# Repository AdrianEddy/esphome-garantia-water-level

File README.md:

# Garantia water tank level sensor for ESPHome / KNX

So you have an old-fashioned water tank level module like this one

and you want to see the percentage in your Home Assistant dashboard? Let's do it!

Three ways to get there:

- **V1** – keep the original controller, sniff its display signals with an ESP32 (below).
- **V2** – replace the controller with a small board that talks to the tank sensor directly:
  analog 0–5 V output (KNX or ESP32 ADC), or ESP32 pulse counting with a single transistor. [Jump to V2](#v2--replacing-the-controller).
- **V3** – a KNX device of its own: one small board on the KNX bus that powers the sensor and reports level, frequency
  and faults straight to KNX, with calibration from Home Assistant and a safe top-up valve control. [Jump to V3](#v3--knx-device).

---

# V1 – reading the original controller

## 0. [What? How?](HOW.md)

## 1. Required hardware
- [ESP32-S3-Zero](https://www.waveshare.com/esp32-s3-zero.htm)
- [TXS0108E](https://aliexpress.com/i/4001172918547.html)

## 2. Connections

You also have to replace the on-board voltage regulator **8L05A** to a more powerful one [KF50BD-TR](https://www.st.com/resource/en/datasheet/kfxx.pdf)

## 3. ESPHome component

```yaml
esphome:
  name: garantia-water-level
  platformio_options: # needed for ESP32-S3
    board_build.flash_mode: dio

esp32:
  board: adafruit_feather_esp32s3
  framework:
    type: esp-idf

external_components:
  - source: github://AdrianEddy/esphome-garantia-water-level
    components: [ garantia-water-level ]

sensor:
  - platform: garantia-water-level
```

## Final assembly

## See it in action

---

# V2 – replacing the controller

The tank-side electronics (the small box in the tank + the red/white sensor cord) are fine and stay untouched.
Only the indoor box gets replaced.

## What the sensor actually does (research, short version)

Reverse-engineered from the original PCB and measured with a scope – **the manual is misleading here**:

- The tank box is a capacitance-to-frequency converter on a **2-wire current loop**: the controller sends +12 V on one RCA contact, the sensor's return current comes back on the other contact through a **110 Ω shunt** (2×220 Ω on the original PCB). The current is pulsed – that's the signal.
- Signal across the shunt: **≈1.7 V pk-pk**, square-ish, ~35/65 duty, on ~3 V DC (the sensor draws ≈27 mA).
- **Frequency: ~145 Hz with an empty tank, ~25 Hz with a full tank.** More water → lower frequency.
  The "200 Hz – 20 kHz" in the manual is *not* what comes down the cable – ignore it.
- Level is **linear in period**, not frequency: `level = (1/f − 1/f_empty) / (1/f_full − 1/f_empty)`.
- The original controller is an ATtiny2313 counting that frequency with its internal comparator. No magic.

Conclusions that saved parts:
- The signal is big enough that **no comparator is needed** – an LM2917 or a single transistor reads it directly.
  (Only if your sensor variant gives < 300 mVpp would you need an LM393-style comparator in front.)
- The one critical component is the LM2917 timing cap C1 – it sets the gain: **C0G / U2J / film only**, never X7R.
- Frequencies are installation specific (cord length, tank). **Measure yours** before picking values.
- If your original controller reads unstable, check its wall adapter first – ours had sagged to 10 V.

## Measure your sensor first

1. Power the tank box with 12 V through a 110 Ω shunt to GND (the V2 board does exactly this).
2. Scope across the shunt, **AC coupling**, 0.5 V/div, 10 ms/div. Note the frequency.
3. Record `f_empty` (pump can't take more out) and `f_full` (water at the overflow). Optional sanity check:
   a period-linear sensor sits at `2 / (1/f_empty + 1/f_full)` at 50 % (≈43 Hz for 145/25).

Everything below is parameterised on `f_empty` and `f_full`.

## Which option?

| You want | Use |
|---|---|
| An **analog 0–5 V signal** – KNX analog input (e.g. ABB AE/A 2.1) or ESP32 ADC | **Option A – LM2917** |
| Just an ESP32 in Home Assistant, best accuracy, fewest parts | **Option B – transistor + `pulse_meter`** |

Common to both: 12 V DC supply, RCA jack (contact A = +12 V feed, contact B = signal), 110 Ω shunt from signal to GND, one common GND.

**Power:** a Mean Well HDR-15-12 works, but in the KNX version I skipped the extra PSU altogether: the **yellow/white pair** of the KNX cable
carries the 30 V *auxiliary* (unchoked) output of the KNX power supply, and **Traco Power TMR 2412** drops it to 12.0 V.
 The board draws ~20 mA at 30 V. Take it only from the auxiliary output / yellow-white pair – **never from the
red/black bus pair**, which carries the telegrams and must not see a switching load. **Do not** use a cheap DC-DC buck module (LM2596-type) - 12V GND MUST be isolated from KNX GND

---

### Option A – LM2917 frequency-to-voltage (KNX / analog)

**KiCad project (schematic + PCB, JLCPCB-ready):** [hardware/garantia-lm2917-kicad.zip](hardware/garantia-lm2917-kicad.zip)
– the 1206/SOIC parts can be assembled by JLCPCB PCBA; DIP LM2917, trimmer and connectors are hand-soldered.

Transfer function: **V_OUT = 7.56 V × f × C1 × R1**. Design for ~4.5 V at `f_empty` (headroom below the 5 V input range):

```
C1 × R1 = 4.5 / (7.56 × f_empty)          # f_empty = 145 Hz → 4.1e-3
pick C1 so R1 lands mid-trimmer (47k fixed + 100k trim):  145 Hz → C1 = 47 nF, R1 ≈ 87 k
charge-pump limit:  f_empty < 140e-6 / (C1 × 7.56)        # 47 nF → 394 Hz max
```

Values as built (f_empty 145 Hz, f_full 25 Hz):

| Ref | Value | Notes |
|---|---|---|
| R1 | 110 Ω (or 2×220 Ω) | shunt |
| C3, R2, R3 | 470 nF film, 22 k, 10 k | AC coupling into pin 1 |
| R4, C4, C5 | 470 Ω, 1 µF, 100 nF | pin 6 (internal 7.56 V zener) |
| C1 | **47 nF C0G / U2J / film** | pin 2 – gain critical |
| R5 + RV1, C2 | 47 k + 100 k trimmer (rheostat), 10 µF | pin 3 – gain trim + filter |
| R6, R7 | 10 k, 470 Ω | output load + series; pin 7 strapped to pin 4, pin 5 to +12 V |

Output: empty 145 Hz → **4.50 V**, full 25 Hz → **0.78 V**. Voltage at level L: `V = 4.5 / (1 + (f_empty/f_full − 1)·L)`.

**Trim:** turn RV1 until `OUT = 4.5 × f / f_empty` at any known frequency (full tank → 0.78 V).

**KNX (ABB AE/A 2.1):** channel = voltage 0–5 V, output as 4-byte float, lower 0 % → 0, upper 100 % → 5 (bus value = volts).
Filter *low* (the 64-sample filter turns a sensor failure into a 60 s fake "filling" ramp). Send on change ≥1 % + cyclic 5 min.
Threshold 1 (valve): ON above 3.04 V (10 %), OFF below 2.86 V (12 %). Threshold 2 (fault): ON below 0.40 V.

**Home Assistant (KNX):**
```yaml
knx:
  sensor:
    - name: "Tank voltage"
      state_address: "5/3/4"
      type: 4byte_float
      device_class: voltage

template:
  - sensor:
      - name: "Rainwater tank level"
        unit_of_measurement: "%"
        state_class: measurement
        state: >
          {% set v = states('sensor.tank_voltage') | float(0) %}
          {% set ve = 4.50 %}   {# voltage at f_empty #}
          {% set vf = 0.78 %}   {# voltage at f_full  #}
          {% if v < 0.4 %}{{ none }}
          {% else %}{{ [0, [100, ((1/v - 1/ve) / (1/vf - 1/ve) * 100) | round(0)] | min] | max }}
          {% endif %}
  - binary_sensor:
      - name: "Rainwater tank sensor fault"
        device_class: problem
        state: "{{ states('sensor.tank_voltage') | float(0) < 0.4 }}"
```

**ESP32 ADC instead of KNX:** 10 k / 10 k divider from OUT to GND, tap → GPIO4 (ADC1), common GND.
```yaml
sensor:
  - platform: adc
    pin: GPIO4
    id: tank_v
    attenuation: 12db
    update_interval: 1s
    filters:
      - median: { window_size: 15, send_every: 5 }
      - multiply: 2.0
  - platform: template
    name: "Rainwater tank level"
    unit_of_measurement: "%"
    lambda: |-
      const float VE = 4.50, VF = 0.78;
      float v = id(tank_v).state;
      if (v < 0.4) return NAN;
      return clamp((1.0f/v - 1.0f/VE) / (1.0f/VF - 1.0f/VE) * 100.0f, 0.0f, 100.0f);
```
(The ESP32 ADC is coarse below ~0.15 V – fine for a tank; KNX or Option B is more accurate near full.)

---

### Option B – one transistor + ESPHome (pulse counting)

```
shunt node ─ 100 nF ─┬─ 10k ─┬─ base Q1 (BC547 / MMBT3904)
                     │       └─ D1 1N4148 (cathode at base, anode GND)
                    100k         emitter → GND
                     │           collector ─┬─ 10k → +3.3 V (from the ESP module)
                    GND                     └─ GPIO4
```
The stage is an edge detector: one ~2 ms low pulse on GPIO4 per sensor cycle. **Keep the coupling cap ≤ 100 nF** – a bigger one merges pulses at high frequency.
Power the ESP32-S3-Zero from USB or a 12 V→5 V buck; common GND with the sensor board.

```yaml
sensor:
  - platform: pulse_meter
    pin:
      number: GPIO4
      mode: INPUT
    id: tank_pulse
    name: "Tank sensor frequency"
    unit_of_measurement: "Hz"
    internal_filter: 500us     # pulses are ~2 ms – do NOT use 2 ms
    timeout: 250ms             # no pulse for 250 ms = sensor fault
    filters:
      - multiply: 0.016667     # pulses/min → Hz
      - sliding_window_moving_average: { window_size: 10, send_every: 5 }

  - platform: template
    name: "Rainwater tank level"
    unit_of_measurement: "%"
    state_class: measurement
    update_interval: 10s
    lambda: |-
      const float F_EMPTY = 145.0, F_FULL = 25.0;   // measure yours
      float f = id(tank_pulse).state;
      if (isnan(f) || f < 5.0) return NAN;
      return clamp((1.0f/f - 1.0f/F_EMPTY) / (1.0f/F_FULL - 1.0f/F_EMPTY) * 100.0f, 0.0f, 100.0f);

binary_sensor:
  - platform: template
    name: "Rainwater tank sensor fault"
    device_class: problem
    lambda: return isnan(id(tank_pulse).state) || id(tank_pulse).state < 5.0;
```

Calibration = two constants. Uniform ~1 % resolution across the whole tank, no trimmer, no critical parts.

---

## Top-up valve

Drive it separately from Home Assistant Automation, using any standard output (KNX, ESPHome relays, Tuya etc)

## Debugging notes (things that cost us time)

- Measure frequency at the **shunt**, not at LM2917 pin 1 – the coupling network droops the waveform at low frequency and confuses scope counters.
- A half-full tank gives only a few hundred mV out of the LM2917 – that is correct, the scale is nonlinear (all the resolution sits at the empty end, where the valve decisions are).
- "Empty" depends on residual water on the probe (we saw 125 vs 145 Hz ≈ 3 % of level). Calibrate to your pump-limit state.

---

# V3 – KNX device

One small board instead of V2 + an analog KNX input module: it plugs into the KNX bus and the 30 V auxiliary pair,
powers the tank sensor itself, measures its frequency and reports the level straight to KNX. No ESP32, no WiFi.

## What it does

- **KNX device on its own:** NCN5130 transceiver + STM32G0B1 running [thelsing/knx](https://github.com/thelsing/knx), powered from the bus (10 mA).
- **Powers the sensor** from the yellow/white 30 V auxiliary pair through a **Traco TMR 2412** (isolated 12 V). The garden cable never becomes part of the KNX line.
- **Reads the sensor like the original controller** (12 V feed, 110 Ω shunt), slices the signal with an LM2903 comparator and sends it across the isolation barrier through an LTV-817S optocoupler.
- **Measures the period against the NCN5130's crystal** (≤ 50 ppm), not the STM32's RC oscillator (up to 3 % off in a cold garage).
- **KNX objects:** level %, frequency, volume, sensor fault, low-level alarm, calibration (write the two frequencies, or press "tank is empty / full now"), and a **top-up valve** with safety limits.
- **Flashing over USB** through the STM32's own ROM bootloader (DFU). No programmer needed.

## How it works

Three galvanically separate domains on a 28 × 46 mm, 4-layer board, kept 2 mm apart on every layer:

```
 KNX bus (red/black) ──► NCN5130 ──► 3.3 V ──► STM32G0B1 ◄── XCLK 8 MHz from the NCN5130's crystal
                                                   ▲
                                                   │  LTV-817S optocoupler (5 kV)
                                                   │
 aux 30 V (yellow/white) ─► TMR 2412 ─► 12 V ─► RCA tip ─► sensor ─► RCA shell ─► 110 Ω shunt ─► LM2903
                            (1.6 kV)                           (floating sensor domain)
```

- **Why isolated:** inside the KNX power supply the aux minus is tied to the bus minus, and the sensor cable lies
  underground in a wet tank. A cheap non-isolated buck would make that cable part of the KNX line (see V2's power note).
- **The RCA shell is the signal**, not ground (as on the original controller), so the jack floats with the sensor domain.
- **The comparator** compares the shunt voltage with its own long-term average (0.5 s), with hysteresis. It needs no
  coupling capacitor, so it works from 25 to 145 Hz alike, and a shorted or open cable simply stops the pulses → "sensor fault".
- **The level** is linear in period: `level = (1/f − 1/f_empty) / (1/f_full − 1/f_empty)` (defaults 145 / 25 Hz, set in ETS or from Home Assistant).

Details, values and reasons: [v3/design.md](v3/design.md).

## Files

| | |
|---|---|
| Design document | [v3/design.md](v3/design.md) |
| KiCad 10 project | [v3/hardware/kicad](v3/hardware/kicad) – schematic, 4-layer PCB, design rules incl. the isolation rules, libraries |
| JLCPCB package | [v3/fab/jlcpcb-2026-10-17-a](v3/fab/jlcpcb-2026-10-17-a) – Gerbers, BOM, CPL, [ORDER-NOTES.md](v3/fab/jlcpcb-2026-10-17-a/ORDER-NOTES.md) |
| Firmware source | [v3/firmware](v3/firmware) – STM32 boot manager + KNX application, `.knxprod` generator, flash kit ([README](v3/firmware/README.md)) |
| Built firmware + `.knxprod` | [v3/release/firmware-1.2](v3/release/firmware-1.2) |

## Building one

- **PCB + assembly:** JLCPCB, 4 layers, both sides assembled (54 SMD parts). Everything to fill in is in
  [ORDER-NOTES.md](v3/fab/jlcpcb-2026-10-17-a/ORDER-NOTES.md). Check the **STM32G0B1KCU6** stock first: it was out of
  stock in October 2026; the KCU7 is a drop-in.
- **Hand-soldered:**
  - 2 × 2 WAGO 243-131 pins for the WAGO 243-211 (bus, red/grey) and 243-212 (aux, yellow/white) plugs;
  - the Traco TMR 2412 (TMR 3-2412 fits);
  - a Keystone 900 RCA jack;
  - a USB-C breakout on J3 for flashing.
- **Before the first power-up:** the ohmmeter checks in [design.md](v3/design.md) ("PCB layout rules", "Hand-soldering").

## Flashing

USB doesn't power the board: put it on the KNX bus (red/black), plug a USB cable into the breakout on J3, and **run the laptop on battery** – J3's ground is the KNX minus.

- **New board:** it starts in DFU by itself → flash `garantia-knx-u3-full.hex`.
- **Updates:** hold the button (SW1) for 3–10 s and release → DFU → flash `garantia-knx-u3-app.hex`.
- `dfu-util -d 0483:df11 -a 0 -s 0x08001000:leave -D garantia-knx-u3-app.bin`, or STM32CubeProgrammer, or the
  portable [flash kit](v3/firmware/flashkit) (Windows + macOS scripts that check everything first).

Full procedure: [v3/firmware/README.md](v3/firmware/README.md#flashing-usb-dfu).

## ETS

Import [garantia-knx.knxprod](v3/release/firmware-1.2/garantia-knx.knxprod) (manufacturer 0x00FA, "Garantia tank level"),
press SW1 briefly (red LED on) to program the individual address, then download the application.
Calibration defaults to 145 Hz empty / 25 Hz full; top-up control and the low-level alarm are off until you enable them.

## Home Assistant (KNX)

```yaml
knx:
  sensor:
    - name: "Rainwater tank level"          # object 1, DPT 8.010 (0.01 %)
      state_address: "5/3/12"
      type: percentV16
      state_class: measurement
      sync_state: init
    - name: "Rainwater tank frequency"      # object 2, DPT 14.033
      state_address: "5/3/13"
      type: frequency
      device_class: frequency
      state_class: measurement
      sync_state: init
    - name: "Rainwater tank volume"         # object 3, DPT 12.1200 (set "Tank volume" in ETS)
      state_address: "5/3/18"
      type: volume_liquid_litre
      device_class: volume_storage
      state_class: measurement
      sync_state: init
  binary_sensor:
    - name: "Rainwater tank sensor fault"   # object 4, DPT 1.005
      state_address: "5/3/17"
      device_class: problem
      sync_state: init
    - name: "Rainwater tank low"            # object 5, DPT 1.005 (set "Low-level alarm below" in ETS)
      state_address: "5/3/16"
      device_class: problem
      sync_state: init
  number:                                   # objects 6/7, DPT 14.033: show and set the calibration
    - name: "Rainwater tank f empty"
      address: "5/3/19"
      state_address: "5/3/19"
      type: frequency
      min: 15
      max: 180
      step: 0.1
      mode: box
    - name: "Rainwater tank f full"
      address: "5/3/20"
      state_address: "5/3/20"
      type: frequency
      min: 15
      max: 180
      step: 0.1
      mode: box
  button:                                   # objects 8/9, DPT 1.017: teach the current frequency
    - name: "Rainwater tank is empty now"
      address: "5/3/15"
      payload: 1
    - name: "Rainwater tank is full now"
      address: "5/3/14"
      payload: 1
```

Use your own group addresses. A teach-in is refused (the number entity then keeps its value) while the reading isn't
valid, e.g. right after power-up or during a sensor fault.

The frequency arrives as a full float, but Home Assistant displays sensors of the `frequency` device class in whole Hz
by default (the KNX integration always gives DPT 14.033 that class). To see the decimals, open the sensor's settings
and set *Display precision*, e.g. 43.27. The level (DPT 8.010) has no device class and shows its decimals as is.

## Top-up valve

Turn on "Top-up valve control" in ETS and link object 10 to a KNX switching actuator channel set to a **staircase /
timeout function** (e.g. 5 min). The board then:

- opens below 10 % and closes at 12 % (adjustable);
- repeats ON every minute while filling, so the valve closes by itself if the board or the bus dies;
- closes on a sensor fault and locks (alarm on object 12) after 30 min of opening per fill, or when the level doesn't rise
  by 1 % within 10 min – a burst pipe or a dry supply doesn't flood the garden;
- is enabled / disabled from Home Assistant through object 11 (switching it off and on again also clears a lock);
- keeps the lock, the enable and the fill time across power cuts.

```yaml
knx:
  switch:
    - name: "Rainwater tank top-up"         # object 11, DPT 1.003
      address: "5/3/21"
      state_address: "5/3/21"
  binary_sensor:
    - name: "Rainwater tank top-up fault"   # object 12, DPT 1.005
      state_address: "5/3/22"
      device_class: problem
```

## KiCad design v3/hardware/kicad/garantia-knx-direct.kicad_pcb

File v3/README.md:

# V3: KNX device

The overview, how it works, ordering, flashing and the Home Assistant configuration are in the main [README, section V3](../README.md#v3--knx-device).

| Folder / file | What |
| --- | --- |
| [`design.md`](design.md) | The design document: sensor facts, architecture and why the sensor domain floats, every sheet with values, pins and LCSC numbers, the floorplan, layout rules, firmware design, the KNX application |
| [`hardware/kicad/`](hardware/kicad/) | KiCad 10 project, the source for the schematic and PCB: 4 sheets, 4-layer PCB, design rules (`.kicad_dru`, including the 2 mm isolation rules), project libraries |
| [`fab/jlcpcb-2026-10-17-a/`](fab/jlcpcb-2026-10-17-a/) | JLCPCB package: Gerbers, BOM, CPL (fitted pad by pad against JLC's footprints), `ORDER-NOTES.md` |
| [`firmware/`](firmware/) | Firmware source (STM32G0B1, thelsing/knx), ETS product generator, flash kit; [`firmware/README.md`](firmware/README.md) |
| [`release/firmware-1.2/`](release/firmware-1.2/) | Built firmware 1.2 images and the signed `.knxprod` (the level in 0.01 % steps) |

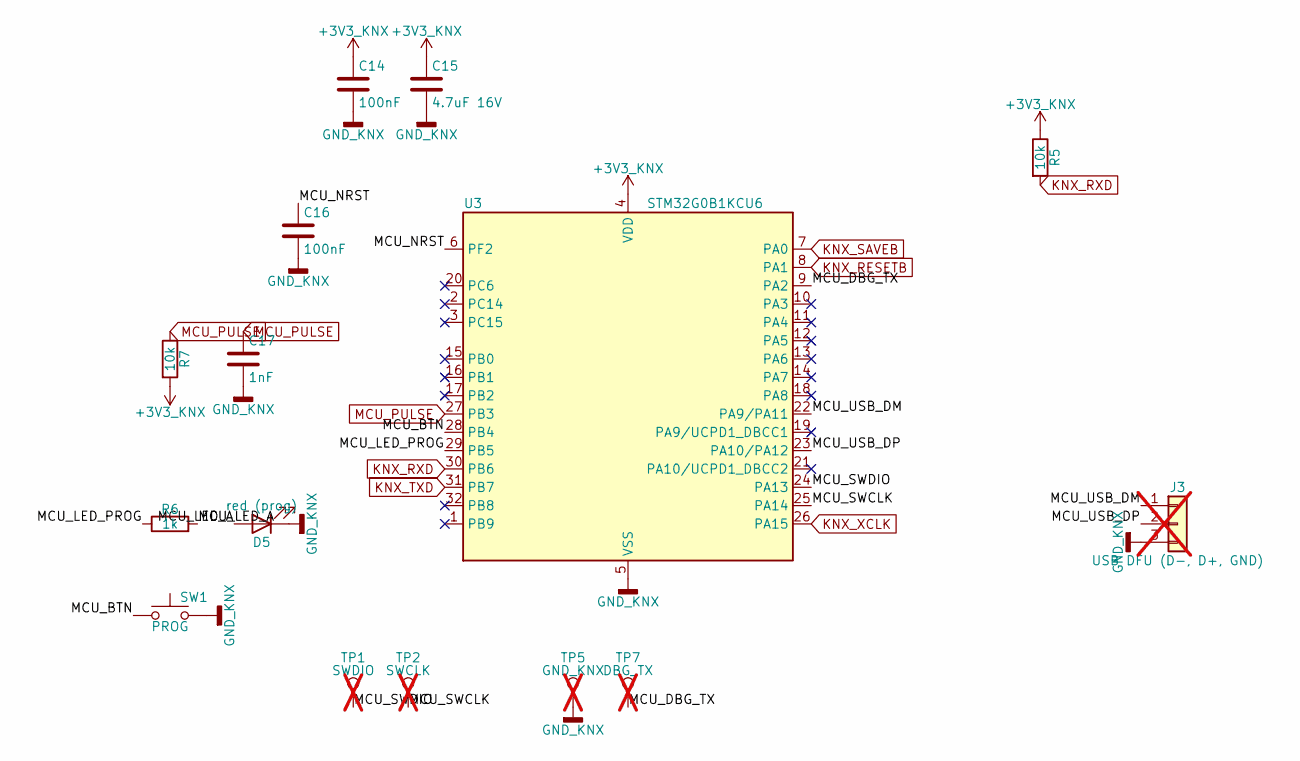
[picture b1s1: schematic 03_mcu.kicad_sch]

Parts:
C14, C16: 100nF; C_0402_1005Metric; MPN CL05B104KB54PNC; LCSC C307331
C15: 4.7uF 16V; C_0603_1608Metric; MPN CL10A475KO8NNNC; LCSC C19666
C17: 1nF; C_0402_1005Metric; MPN 0402B102K500NT; LCSC C1523
D5: red (prog); LED_0603_1608Metric; MPN KT-0603R; LCSC C2286
J3: USB DFU (D-, D+, GND); PinHeader_1x03_P2.54mm_Vertical; MPN 3 plated holes for a USB-C breakout (D-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; not fitted
R5, R7: 10k; R_0402_1005Metric; MPN 0402WGF1002TCE; LCSC C25744
R6: 1k; R_0402_1005Metric; MPN 0402WGF1001TCE; LCSC C11702
SW1: PROG; SW_SPST_TS-1088-xR020; MPN TS-1088-AR02016; LCSC C720477
TP1: SWDIO; TestPoint_Pad_D1.0mm; MPN test pad, not assembled; not fitted
TP2: SWCLK; TestPoint_Pad_D1.0mm; MPN test pad, not assembled; not fitted
TP5: GND_KNX; TestPoint_Pad_D1.0mm; MPN test pad, not assembled; not fitted
TP7: DBG_TX; TestPoint_Pad_D1.0mm; MPN test pad, not assembled; not fitted
U3: STM32G0B1KCU6; QFN-32-1EP_5x5mm_P0.5mm_EP3.45x3.45mm; MPN STM32G0B1KCU6; LCSC C5270237

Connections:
+3V3_KNX: C14.1, C15.1, R5.1, R7.2, U3.4 (VDD); also elsewhere on the board
/3 MCU/MCU_BTN: SW1.1, U3.28 (PB4)
/3 MCU/MCU_DBG_TX: TP7.1 (1_1), U3.9 (PA2)
/3 MCU/MCU_LED_A: D5.2 (A), R6.2
/3 MCU/MCU_LED_PROG: R6.1, U3.29 (PB5)
/3 MCU/MCU_NRST: C16.1, U3.6 (PF2)
/3 MCU/MCU_SWCLK: TP2.1 (1_1), U3.25 (PA14)
/3 MCU/MCU_SWDIO: TP1.1 (1_1), U3.24 (PA13)
/3 MCU/MCU_USB_DM: J3.1, U3.22 (PA9/PA11)
/3 MCU/MCU_USB_DP: J3.2, U3.23 (PA10/PA12)
GND_KNX: C14.2, C15.2, C16.2, C17.2, D5.1 (K), J3.3, SW1.2, TP5.1 (1_1), U3.5 (VSS), U3.33 (VSS); also elsewhere on the board
KNX_RESETB: U3.8 (PA1); also elsewhere on the board
KNX_RXD: R5.2, U3.30 (PB6); also elsewhere on the board
KNX_SAVEB: U3.7 (PA0); also elsewhere on the board
KNX_TXD: U3.31 (PB7); also elsewhere on the board
KNX_XCLK: U3.26 (PA15); also elsewhere on the board
MCU_PULSE: C17.1, R7.1, U3.27 (PB3); also elsewhere on the board

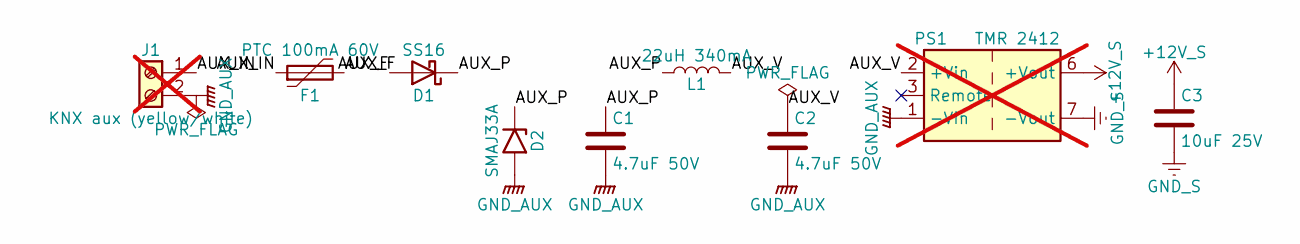
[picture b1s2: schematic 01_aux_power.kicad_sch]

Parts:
C1, C2: 4.7uF 50V; C_1210_3225Metric; MPN GRM32ER71H475KA88L; LCSC C86052
C3: 10uF 25V; C_0805_2012Metric; MPN CL21A106KAYNNNE; LCSC C15850
D1: SS16; D_SMA; MPN SS16; LCSC C2481
D2: SMAJ33A; D_SMA; MPN SMAJ33A; LCSC C113966
F1: PTC 100mA 60V; Fuse_1206_3216Metric; MPN BSMD1206-010-60V; LCSC C883116
J1: KNX aux (yellow/white); KNX_BusPins_2x1.0mm_P5.75mm_WAGO_243-211_Top; MPN 2x WAGO 243-131 1.0 mm solder pin (LCSC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; not fitted
L1: 22uH 340mA; L_APV_AHW2012FE; MPN AHW2012FE220KTF; LCSC C6364733
PS1: TMR 2412; Converter_DCDC_TRACO_TEC2-12xxWI_24xxWI_48xxWI_THT; MPN Traco TMR 2412 (TMR 3-2412 fits), hand-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; not fitted

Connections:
+12V_S: C3.1, PS1.6 (+Vout); also elsewhere on the board
/1 Aux power/AUX_F: D1.2 (A), F1.2
/1 Aux power/AUX_IN: F1.1, J1.1
/1 Aux power/AUX_P: C1.1, D1.1 (K), D2.1 (A1), L1.1
/1 Aux power/AUX_V: C2.1, L1.2, PS1.2 (+Vin)
GND_AUX: C1.2, C2.2, D2.2 (A2), J1.2, PS1.1 (-Vin)
GND_S: C3.2, PS1.7 (-Vout); also elsewhere on the board

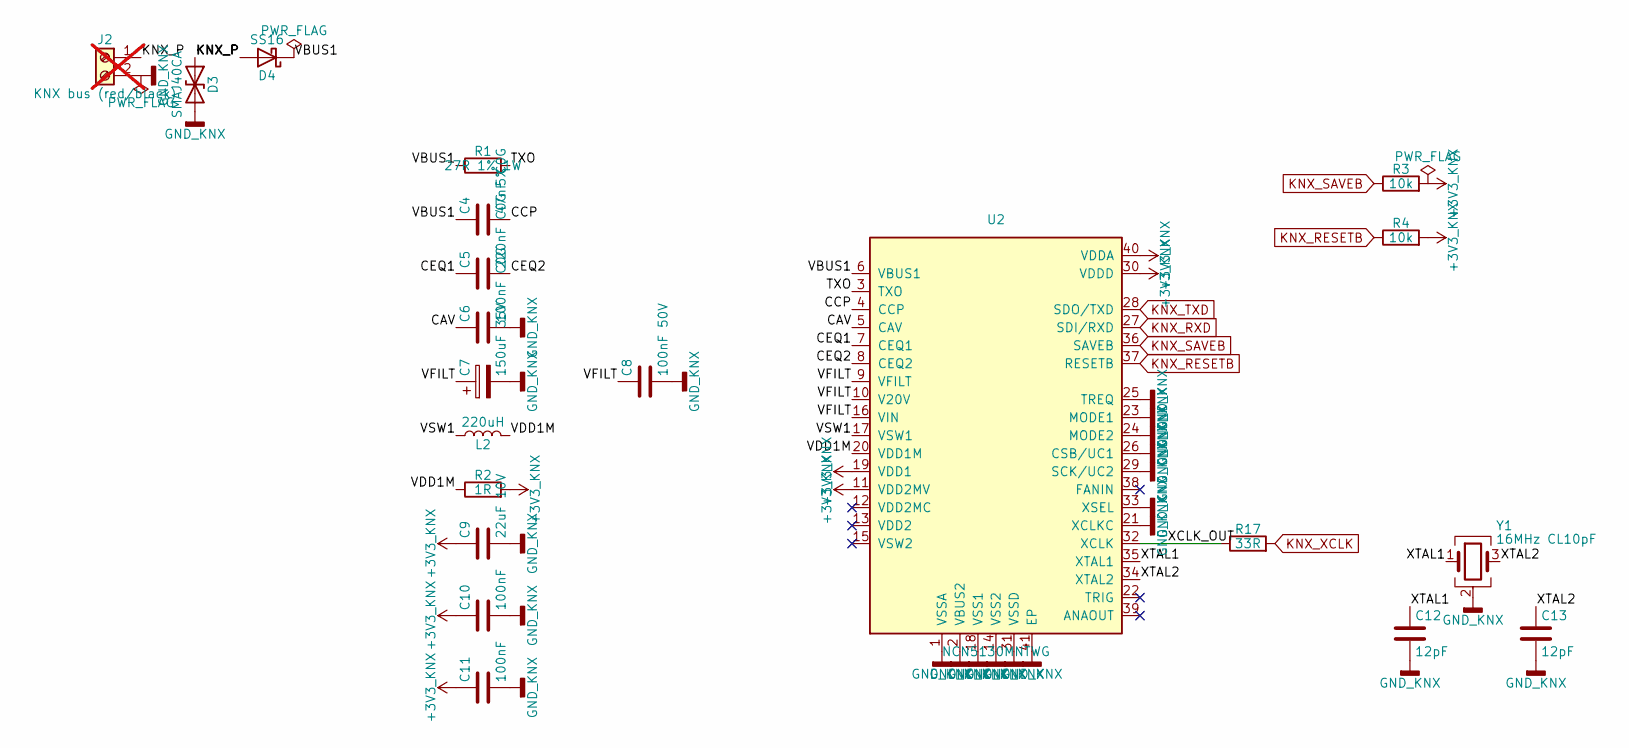
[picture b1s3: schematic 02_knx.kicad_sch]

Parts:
C4: 47nF C0G; C_1206_3216Metric; MPN GRM31M5C1H473JA01L; LCSC C21812
C5: 220nF C0G 5%; C_1206_3216Metric; MPN GRM31C5C1H224JE02L; LCSC C464977
C6: 100nF C0G; C_1206_3216Metric; MPN 1206N104J500CT; LCSC C170182
C7: 150uF 35V; CP_Elec_8x10; MPN EEH-ZA1V151P; LCSC C341199
C8: 100nF 50V; C_0603_1608Metric; MPN CC0603KRX7R9BB104; LCSC C14663
C9: 22uF 10V; C_0805_2012Metric; MPN GRM21BZ71A226ME15L; LCSC C907991
C10, C11: 100nF; C_0402_1005Metric; MPN CL05B104KB54PNC; LCSC C307331
C12, C13: 12pF; C_0402_1005Metric; MPN 0402CG120J500NT; LCSC C1547
D3: SMAJ40CA; D_SMA; MPN SMAJ40CA; LCSC C113970
D4: SS16; D_SMA; MPN SS16; LCSC C2481
J2: KNX bus (red/black); KNX_BusPins_2x1.0mm_P5.75mm_WAGO_243-211_Top; MPN 2x WAGO 243-131 1.0 mm solder pin (LCSC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; not fitted
L2: 220uH; L_Sunlord_SWPA5040S; MPN SWPA5040S221MT; LCSC C370497
R1: 27R 1% 1W; R_2512_6332Metric; MPN RC2512FK-0727RL; LCSC C877905
R2: 1R; R_0402_1005Metric; MPN FRC0402F1R00TS; LCSC C2909329
R3, R4: 10k; R_0402_1005Metric; MPN 0402WGF1002TCE; LCSC C25744
R17: 33R; R_0402_1005Metric; MPN 0402WGF330JTCE; LCSC C25105
U2: NCN5130MNTWG; onsemi_QFN-40-1EP_6x6mm_P0.5mm_EP3.2x3.2mm_ThermalVias; MPN NCN5130MNTWG; LCSC C513000
Y1: 16MHz CL10pF; Crystal_SMD_3225-4Pin_3.2x2.5mm; MPN X322516MMB4SI; LCSC C112972

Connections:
+3V3_KNX: C9.1, C10.1, C11.1, R2.2, R3.2, R4.2, U2.11 (VDD2MV), U2.19 (VDD1), U2.30 (VDDD), U2.40 (VDDA); also elsewhere on the board
/2 KNX bus interface/CAV: C6.1, U2.5 (CAV)
/2 KNX bus interface/CCP: C4.2, U2.4 (CCP)
/2 KNX bus interface/CEQ1: C5.1, U2.7 (CEQ1)
/2 KNX bus interface/CEQ2: C5.2, U2.8 (CEQ2)
/2 KNX bus interface/KNX_P: D3.1 (A1), D4.2 (A), J2.1
/2 KNX bus interface/TXO: R1.2, U2.3 (TXO)
/2 KNX bus interface/VBUS1: C4.1, D4.1 (K), R1.1, U2.6 (VBUS1)
/2 KNX bus interface/VDD1M: L2.2, R2.1, U2.20 (VDD1M)
/2 KNX bus interface/VFILT: C7.1, C8.1, U2.9 (VFILT), U2.10 (V20V), U2.16 (VIN)
/2 KNX bus interface/VSW1: L2.1, U2.17 (VSW1)
/2 KNX bus interface/XCLK_OUT: R17.1, U2.32 (XCLK)
/2 KNX bus interface/XTAL1: C12.1, U2.35 (XTAL1), Y1.1
/2 KNX bus interface/XTAL2: C13.1, U2.34 (XTAL2), Y1.3
GND_KNX: C6.2, C7.2, C8.2, C9.2, C10.2, C11.2, C12.2, C13.2, D3.2 (A2), J2.2, U2.1 (VSSA), U2.2 (VBUS2), U2.14 (VSS2), U2.18 (VSS1), U2.21 (XCLKC), U2.23 (MODE1), U2.24 (MODE2), U2.25 (TREQ), U2.26 (CSB/UC1), U2.29 (SCK/UC2), U2.31 (VSSD), U2.33 (XSEL), U2.41 (EP), Y1.2 (G), Y1.4 (G); also elsewhere on the board
KNX_RESETB: R4.1, U2.37 (RESETB); also elsewhere on the board
KNX_RXD: U2.27 (SDI/RXD); also elsewhere on the board
KNX_SAVEB: R3.1, U2.36 (SAVEB); also elsewhere on the board
KNX_TXD: U2.28 (SDO/TXD); also elsewhere on the board
KNX_XCLK: R17.2; also elsewhere on the board

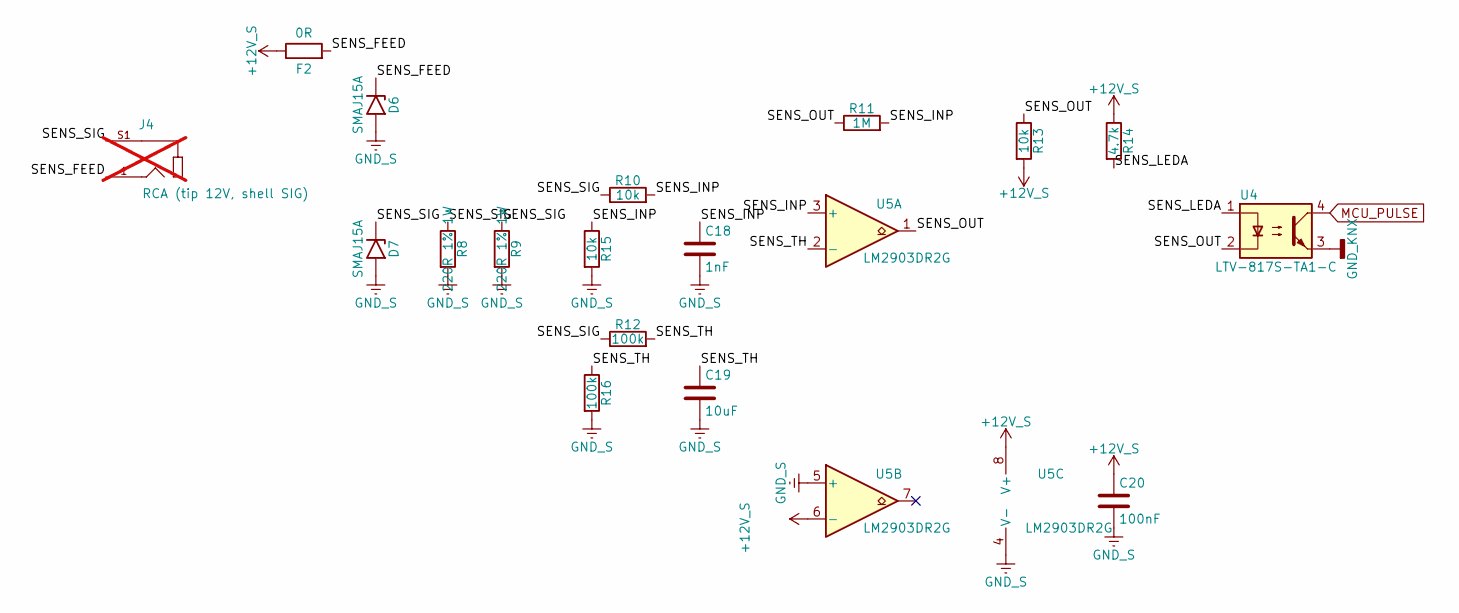
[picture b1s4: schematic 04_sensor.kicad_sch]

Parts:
C18: 1nF; C_0402_1005Metric; MPN 0402B102K500NT; LCSC C1523
C19: 10uF; C_0805_2012Metric; MPN CL21A106KAYNNNE; LCSC C15850
C20: 100nF; C_0402_1005Metric; MPN CL05B104KB54PNC; LCSC C307331
D6, D7: SMAJ15A; D_SMA; MPN SMAJ15A; LCSC C19077535
F2: 0R; R_1206_3216Metric; MPN 1206W4F0000T5E; LCSC C17888
J4: RCA (tip 12V, shell SIG); KEYSTONE_900; MPN Keystone 900 (owner's stock), hand-fitt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; not fitted
R8, R9: 220R 1% 1W; R_2512_6332Metric; MPN 25121WF2200T4E; LCSC C421609
R10, R13, R15: 10k; R_0402_1005Metric; MPN 0402WGF1002TCE; LCSC C25744
R11: 1M; R_0402_1005Metric; MPN 0402WGF1004TCE; LCSC C26083
R12, R16: 100k; R_0402_1005Metric; MPN 0402WGF1003TCE; LCSC C25741
R14: 4.7k; R_0402_1005Metric; MPN 0402WGF4701TCE; LCSC C25900
U4: LTV-817S-TA1-C; SMDIP-4_W9.53mm; MPN LTV-817S-TA1-C; LCSC C109227
U5: LM2903DR2G; SOIC-8_3.9x4.9mm_P1.27mm; MPN LM2903DR2G; LCSC C57474

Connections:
+12V_S: C20.1, F2.1, R13.2, R14.1, U5.6 (-), U5.8 (V+); also elsewhere on the board
/4 Sensor/SENS_FEED: D6.1 (A1), F2.2, J4.1
/4 Sensor/SENS_INP: C18.1, R10.2, R11.2, R15.1, U5.3 (+)
/4 Sensor/SENS_LEDA: R14.2, U4.1
/4 Sensor/SENS_OUT: R11.1, R13.1, U4.2, U5.1
/4 Sensor/SENS_SIG: D7.1 (A1), J4.S1, J4.S2, J4.S3, R8.1, R9.1, R10.1, R12.1
/4 Sensor/SENS_TH: C19.1, R12.2, R16.1, U5.2 (-)
GND_KNX: U4.3; also elsewhere on the board
GND_S: C18.2, C19.2, C20.2, D6.2 (A2), D7.2 (A2), R8.2, R9.2, R15.2, R16.2, U5.4 (V-), U5.5 (+); also elsewhere on the board
MCU_PULSE: U4.4; also elsewhere on the board

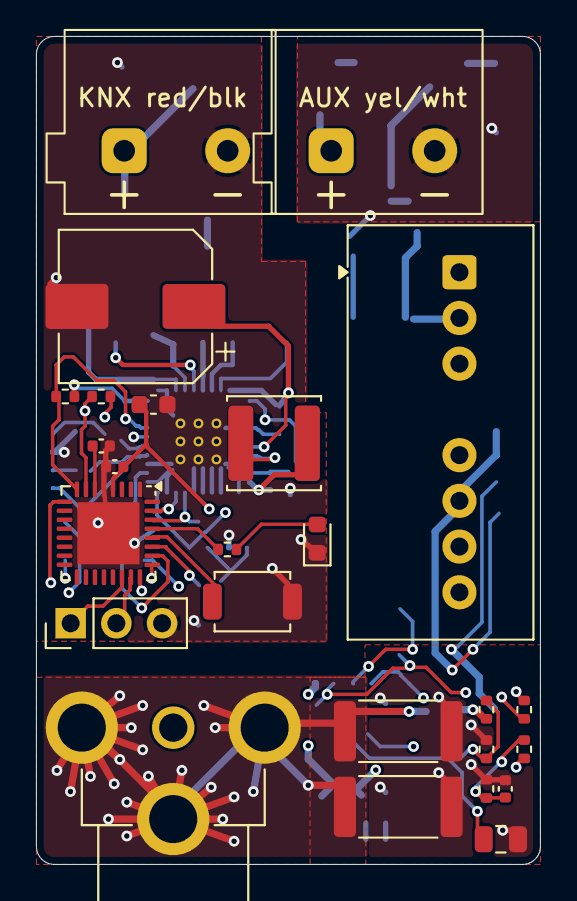
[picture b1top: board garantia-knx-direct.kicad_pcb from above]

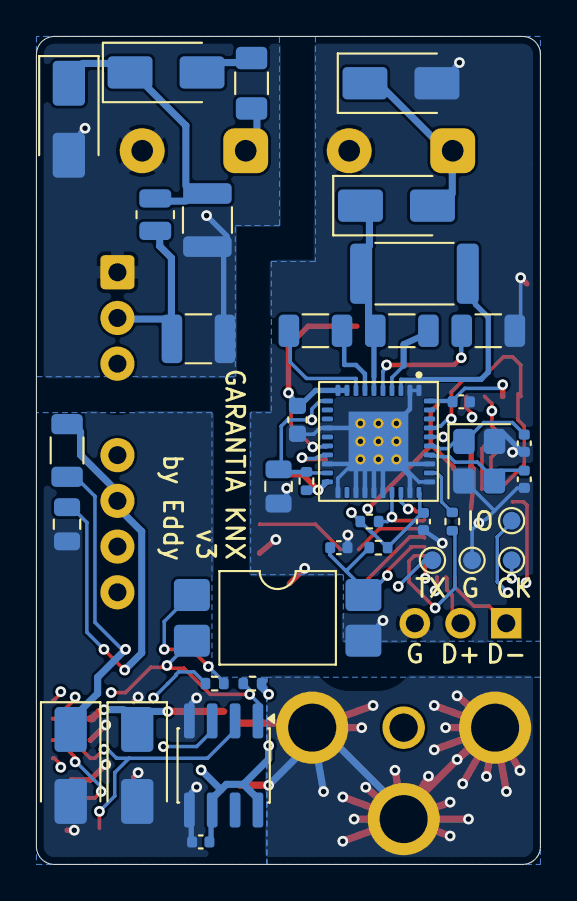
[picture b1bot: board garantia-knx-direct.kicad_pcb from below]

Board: 4 copper layers, 28.0 x 46.0 mm, 63 parts (38 on the bottom side), 43 nets.

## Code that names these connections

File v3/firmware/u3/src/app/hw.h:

/*
 * hw.h: U3 (STM32G0B1KCU6) hardware layer for the application. Based on knx-rgbic's U9 hw layer.
 *
 * Pins (design.md "U3 pin map")
 *   PB6  USART1_TX (AF0) -> KNX_RXD -> NCN5130 SDI/RXD (R5 pull-up)
 *   PB7  USART1_RX (AF0) <- KNX_TXD (NCN5130 SDO/TXD)
 *   PA0  KNX_SAVEB (input, R3 pull-up), PA1 KNX_RESETB (input, R4 pull-up)
 *   PA2  USART2_TX (AF1) -> TP7, debug log, 115200 8N1
 *   PA15 TIM2_ETR (AF2) <- KNX_XCLK (NCN5130 XCLK, 8 MHz, through R17)
 *   PB3  TIM2_CH2 (AF2) <- MCU_PULSE (U4 collector, R7 pull-up, C17)
 *   PB4  MCU_BTN, SW1 to GND_KNX (internal pull-up); PB5 MCU_LED_PROG -> R6 -> D5
 *   PA11/PA12 USB (ROM DFU only), PA13/PA14 SWD; everything else is unconnected and stays analog.
 * Clock: HSI16, no PLL. KNX timing comes from the NCN's crystal; so does the sensor timing (TIM2 on XCLK).
 */
#ifndef HW_H
#define HW_H

#include <stdint.h>
#include <stddef.h>

#ifdef __cplusplus
extern "C" {
#endif

#define HW_SYSCLK_HZ     16000000u
#define HW_KNX_BAUD      19200u      /* NCN5130 UC1/UC2 strapped low: 19200 baud, 9-bit (8E1) */
#define HW_DBG_BAUD      115200u

void     hw_init(void);
uint32_t hw_millis(void);
void     hw_delay_us(uint32_t us);

/* Independent watchdog, about 2 s. */
void     hw_iwdg_start(void);
void     hw_iwdg_refresh(void);

/* USART1: NCN5130. RX bytes are buffered by the interrupt, which then calls the hook (thelsing's ISR path). */
void     hw_knx_uart_open(void);
void     hw_knx_uart_close(void);
int      hw_knx_uart_read(void);                 /* -1 if empty */
size_t   hw_knx_uart_available(void);
size_t   hw_knx_uart_write(const uint8_t* p, size_t n);  /* interrupt-safe, all or nothing */
int      hw_knx_uart_overflow(void);             /* returns and clears the overflow flag */
void     hw_knx_uart_flush(void);                /* waits until everything is on the wire */
uint32_t hw_knx_uart_errors(void);               /* parity, framing, noise (counted, bytes still delivered) */
int      hw_knx_uart_last_error(void);           /* 1 if the byte last read had a parity, framing or noise error */
typedef void (*hw_isr_hook_t)(void);
void     hw_knx_uart_set_rx_hook(hw_isr_hook_t hook);

/* USART2 TX: debug log on TP7. Drops what doesn't fit; never blocks. */
void     hw_dbg_write(const char* s, size_t n);
void     hw_dbg_flush(void);

/* Inputs from the NCN5130 (through R3/R4 pull-ups) */
int      hw_saveb(void);                         /* 1 = high (bus OK, NCN in Normal state) */
int      hw_resetb(void);

/* SW1 and D5 */
int      hw_button(void);                        /* 1 = pressed */
void     hw_led(int on);

/* Flash, bank 2 data only: the KNX area (U3_KNX_DATA_*) and the store pages (U3_STORE_*). */
int      hw_flash_erase_page(uint32_t addr);     /* 0 = ok */
int      hw_flash_program(uint32_t addr, const uint8_t* data, uint32_t len);  /* addr and len multiple of 8 */
void     hw_erase_all_data(void);                /* factory reset: KNX area and store */
/* Mark the bank-2 area about to be read (HW_AREA_NONE when done). A flash ECC double error during the read
 * erases that area, whatever FLASH_ECC2R's address field means (review F-02, O-4, G-9). */
#define HW_AREA_NONE   0u
#define HW_AREA_KNX    1u
#define HW_AREA_STORE0 2u                         /* store page 0; page 1 is HW_AREA_STORE0 + 1 */
#define HW_AREA_STORE1 3u
void     hw_flash_read_area(uint8_t area);
int      hw_take_store_lost(void);               /* 1 once if the ECC NMI erased the store before this start */

uint32_t hw_uid_hash(void);                      /* 32-bit digest of the 96-bit unique ID */

/* Reset cause as found by the boot manager */
#define HW_RESET_POWER    0x01u
#define HW_RESET_IWDG     0x02u
#define HW_RESET_SOFTWARE 0x04u
#define HW_RESET_PIN      0x08u
#define HW_RESET_OTHER    0x10u
#define HW_RESET_DFU      0x20u                  /* the boot manager came from the ROM bootloader (DFU leave) */
uint8_t  hw_reset_cause(void);
uint16_t hw_boot_version(void);                  /* 0 if no boot manager descriptor */

void     hw_reset(void) __attribute__((noreturn));
void     hw_reset_to_bootloader(void) __attribute__((noreturn));  /* via the boot manager: USB DFU */

#ifdef __cplusplus
}
#endif

#endif /* HW_H */

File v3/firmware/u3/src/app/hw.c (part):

/* hw.c: see hw.h. The KNX UART and flash code are knx-rgbic's U9 hw.c with USART1 on PB6/PB7 instead of
 * USART4 on PA0/PA1; the ESP32 link is replaced by a transmit-only debug log. */
#include "hw.h"
#include "stm32g0xx.h"
#include "../shared/u3_shared.h"
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{
    USART_TypeDef* u = USART1;
    RCC->APBENR2 |= RCC_APBENR2_USART1EN;
    gpio_af(GPIOB, 6, 0, 0);            /* R5 holds KNX_RXD high while this pin isn't driven */
    gpio_af(GPIOB, 7, 0, 1);            /* weak pull-up: NCN TXD is push-pull, this only covers its reset */
    s_knx_rx.head = s_knx_rx.tail = 0;
    s_knx_tx.head = s_knx_tx.tail = 0;
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    RCC->IOPENR |= RCC_IOPENR_GPIOAEN | RCC_IOPENR_GPIOBEN;
    RCC->APBENR2 |= RCC_APBENR2_SYSCFGEN;

    /* UCPD dead-battery pull-downs off: PA9/PA10 are left open (design.md U3 pin map). */
    SYSCFG->CFGR1 |= SYSCFG_CFGR1_UCPD1_STROBE | SYSCFG_CFGR1_UCPD2_STROBE;

    /* A reset after the ROM bootloader must boot the application, not the bootloader (AN2606). */
    FLASH->ACR &= ~FLASH_ACR_PROGEMPTY;

    /* Unused pins stay analog (reset state). PA11/PA12 (USB, no pull-ups on this board) stay analog too. */
    gpio_input(GPIOA, 0, 0);            /* KNX_SAVEB, R3 */
    gpio_input(GPIOA, 1, 0);            /* KNX_RESETB, R4 */
    gpio_input(GPIOB, 4, 1);            /* SW1, internal pull-up */
    gpio_output(GPIOB, 5);              /* D5 off */

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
